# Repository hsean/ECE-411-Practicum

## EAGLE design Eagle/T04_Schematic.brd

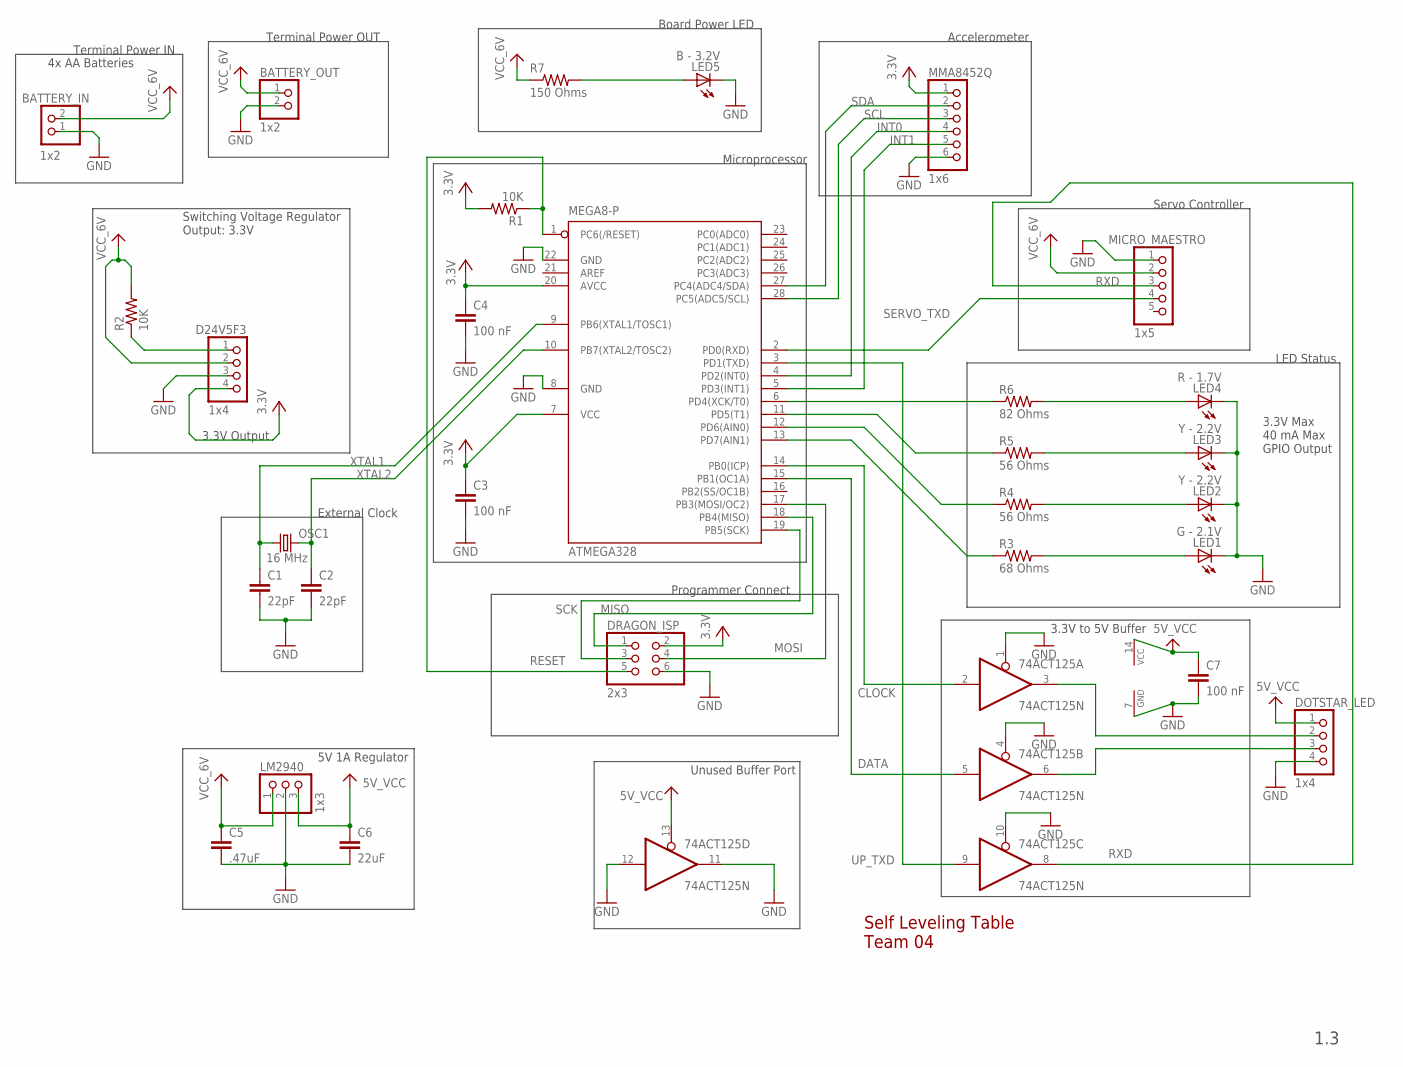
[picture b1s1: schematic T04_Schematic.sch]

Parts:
74ACT125: 74ACT125N; DIL14
ATMEGA328: MEGA8-P; DIL28-3
BATTERY_IN: 1x2; 1X02
BATTERY_OUT: 1x2; 1X02
C1, C2: 22pF; C1206
C3, C4, C7: 100 nF; C1206
C5: .47uF; C1206
C6: 22uF; C1206
D24V5F3: 1x4; 1X04
DOTSTAR_LED: 1x4; 1X04
DRAGON_ISP: 2x3; 2X03
LED1: G - 2.1V; 1206
LED2, LED3: Y - 2.2V; 1206
LED4: R - 1.7V; 1206
LED5: B - 3.2V; 1206
LM2940: 1x3; 1X03
MICRO_MAESTRO: 1x5; 1X05
MMA8452Q: 1x6; 1X06
OSC1: 16 MHz; HC49US
R1, R2: 10K; M1206
R3: 68 Ohms; R1206
R4, R5: 56 Ohms; R1206
R6: 82 Ohms; R1206
R7: 150 Ohms; R1206

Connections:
5V_VCC: 74ACT125.13 (OE), 74ACT125.14 (VCC), C6.1, C7.1, DOTSTAR_LED.1, LM2940.3
CLOCK: 74ACT125.2 (I), ATMEGA328.14 (PB0(ICP))
DATA: 74ACT125.5 (I), ATMEGA328.15 (PB1(OC1A))
GND: 74ACT125.1 (OE), 74ACT125.4 (OE), 74ACT125.7 (GND), 74ACT125.10 (OE), 74ACT125.11 (O), 74ACT125.12 (I), ATMEGA328.8 (GND), ATMEGA328.22 (GND), BATTERY_IN.1, BATTERY_OUT.2, C1.2, C2.2, C3.2, C4.2, C5.2, C6.2, C7.2, D24V5F3.3, DOTSTAR_LED.4, DRAGON_ISP.6, LED1.C, LED2.C, LED3.C, LED4.C, LED5.C, LM2940.2, MICRO_MAESTRO.1, MMA8452Q.6
INT0: ATMEGA328.4 (PD2(INT0)), MMA8452Q.4
INT1: ATMEGA328.5 (PD3(INT1)), MMA8452Q.5
MISO: ATMEGA328.18 (PB4(MISO)), DRAGON_ISP.1
MOSI: ATMEGA328.17 (PB3(MOSI/OC2)), DRAGON_ISP.4
unnamed: LED5.A, R7.2
unnamed: LED1.A, R3.2
unnamed: LED2.A, R4.2
unnamed: LED3.A, R5.2
unnamed: LED4.A, R6.2
unnamed: 74ACT125.3 (O), DOTSTAR_LED.2
unnamed: ATMEGA328.11 (PD5(T1)), R5.1
unnamed: ATMEGA328.12 (PD6(AIN0)), R4.1
unnamed: ATMEGA328.6 (PD4(XCK/T0)), R6.1
unnamed: ATMEGA328.13 (PD7(AIN1)), R3.1
unnamed: 74ACT125.6 (O), DOTSTAR_LED.3
RESET: ATMEGA328.1 (PC6(/RESET)), DRAGON_ISP.5, R1.1
RXD: 74ACT125.8 (O), MICRO_MAESTRO.3
SCK: ATMEGA328.19 (PB5(SCK)), DRAGON_ISP.3
SCL: ATMEGA328.28 (PC5(ADC5/SCL)), MMA8452Q.3
SDA: ATMEGA328.27 (PC4(ADC4/SDA)), MMA8452Q.2
SERVO_TXD: ATMEGA328.2 (PD0(RXD)), MICRO_MAESTRO.4
UP_TXD: 74ACT125.9 (I), ATMEGA328.3 (PD1(TXD))
VCC: ATMEGA328.7 (VCC), ATMEGA328.20 (AVCC), C3.1, C4.1, D24V5F3.4, DRAGON_ISP.2, MMA8452Q.1, R1.2
VCC_6V: BATTERY_IN.2, BATTERY_OUT.1, C5.1, D24V5F3.2, LM2940.1, MICRO_MAESTRO.2, R2.2, R7.1
V_REG_RESET: D24V5F3.1, R2.1
XTAL1: ATMEGA328.9 (PB6(XTAL1/TOSC1)), C1.1, OSC1.1
XTAL2: ATMEGA328.10 (PB7(XTAL2/TOSC2)), C2.1, OSC1.2

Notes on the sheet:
4x AA Batteries
1.3
3.3V Max 40 mA Max GPIO Output
3.3V Output
Terminal Power IN
Terminal Power OUT
Switching Voltage Regulator Output: 3.3V
Self Leveling Table Team 04
Accelerometer
Servo Controller
LED Status
Programmer Connect
Microprocessor
Board Power LED
External Clock
3.3V to 5V Buffer
5V 1A Regulator
Unused Buffer Port

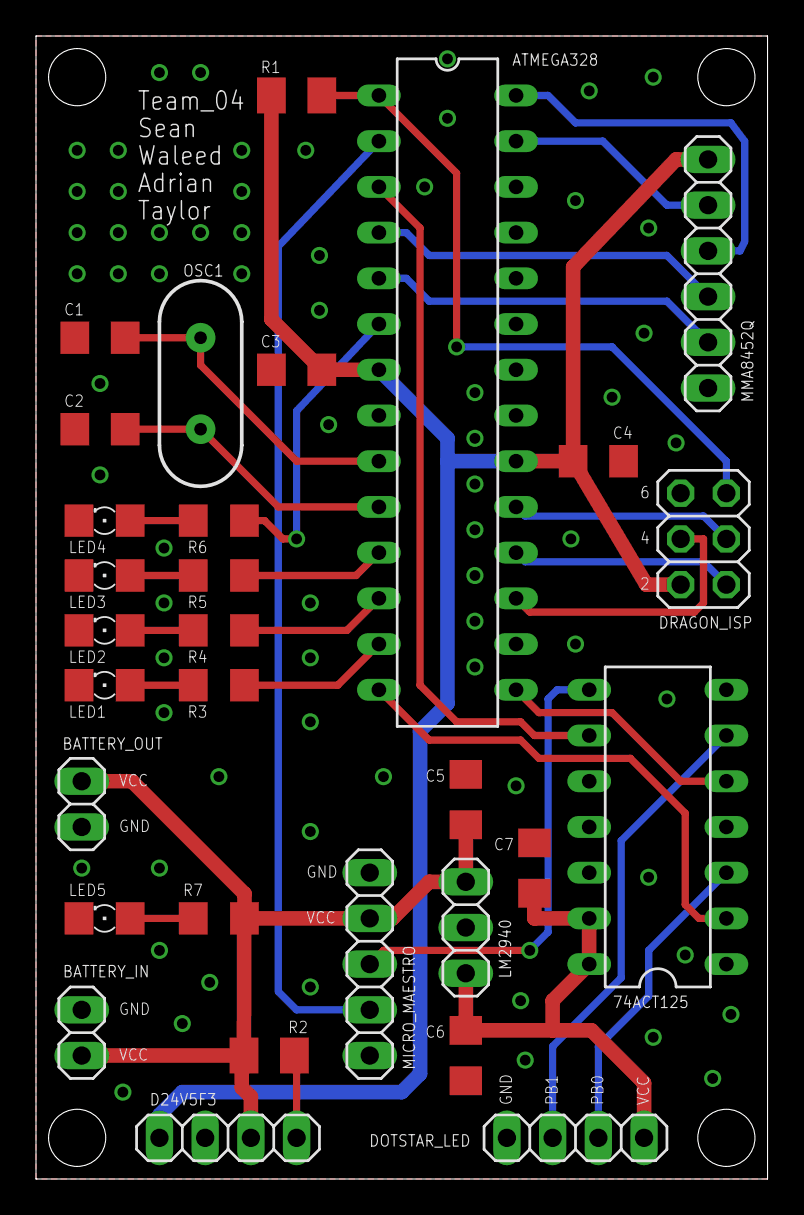
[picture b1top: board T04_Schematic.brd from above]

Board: 2 copper layers, 40.6 x 63.5 mm, 30 parts (0 on the bottom side), 31 nets.

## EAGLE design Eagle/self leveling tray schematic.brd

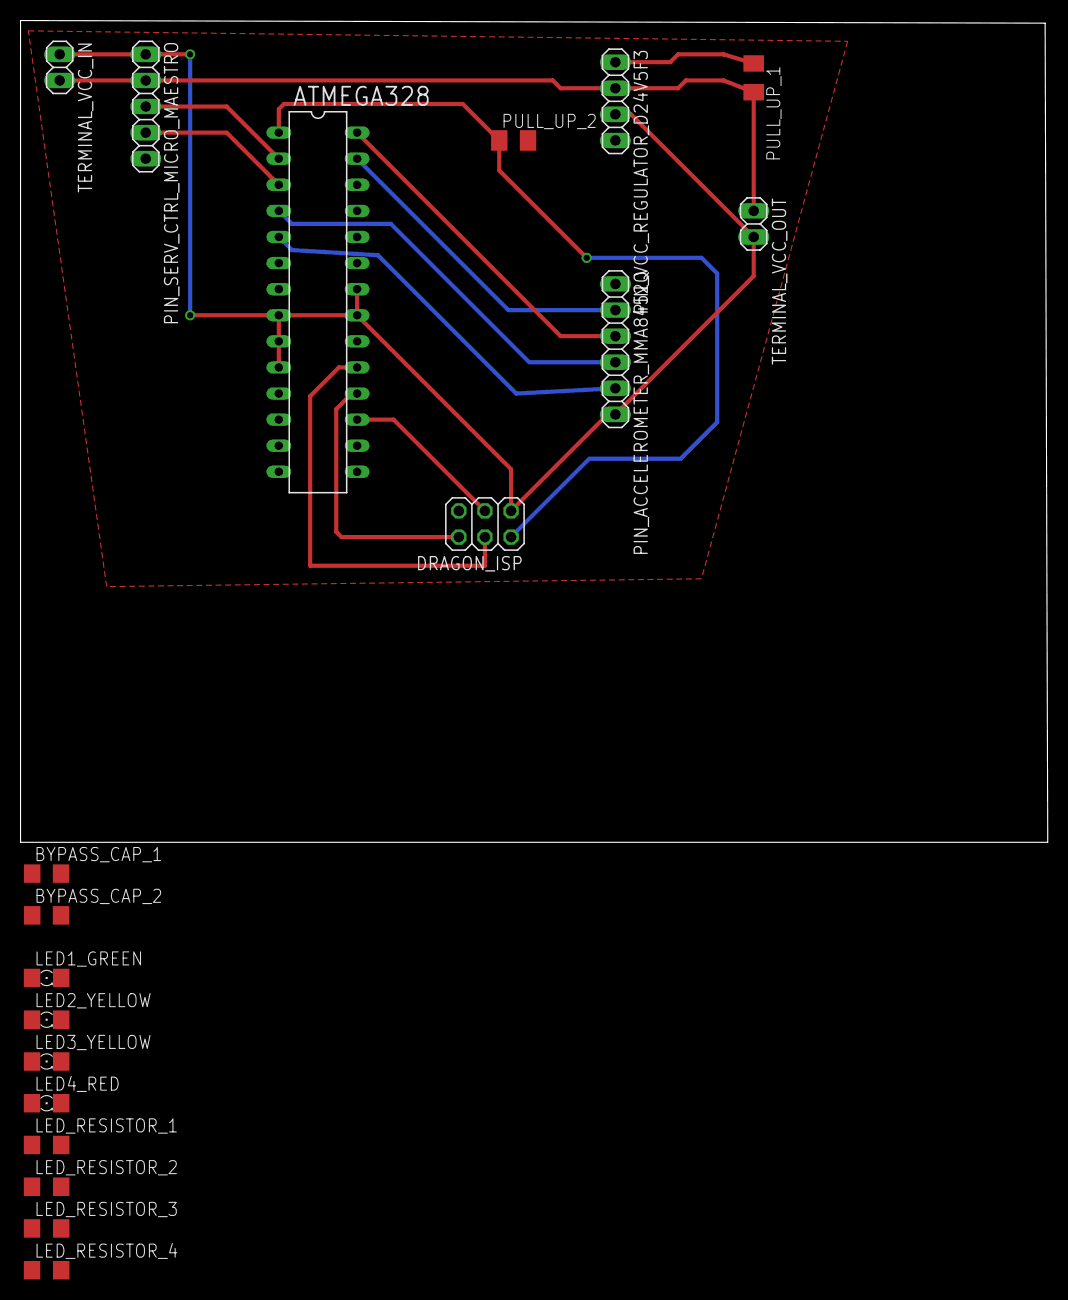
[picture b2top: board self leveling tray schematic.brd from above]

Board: 2 copper layers, 100.0 x 80.0 mm, 19 parts (0 on the bottom side), 22 nets.

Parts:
ATMEGA328: MEGA8-P; DIL28-3
BYPASS_CAP_1, BYPASS_CAP_2: 100 nF; C1206
DRAGON_ISP: 2x3; 2X03
LED1_GREEN, LED2_YELLOW, LED3_YELLOW, LED4_RED: TBD Voltage; 1206
LED_RESISTOR_1, LED_RESISTOR_2, LED_RESISTOR_3, LED_RESISTOR_4: TBD Resistance; R1206
PIN_ACCELEROMETER_MMA8452Q: 1x6; 1X06
PIN_SERV_CTRL_MICRO_MAESTRO: 1x5; 1X05
PIN_VCC_REGULATOR_D24V5F3: 1x4; 1X04
PULL_UP_1, PULL_UP_2: 10K; M1206
TERMINAL_VCC_IN: 1x2; 1X02
TERMINAL_VCC_OUT: 1x2; 1X02

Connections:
6V_BATTERY_VCC: PIN_SERV_CTRL_MICRO_MAESTRO.2, PIN_VCC_REGULATOR_D24V5F3.2, PULL_UP_1.2, TERMINAL_VCC_IN.2, TERMINAL_VCC_OUT.1
GND: ATMEGA328.8, ATMEGA328.9, ATMEGA328.10, ATMEGA328.14, ATMEGA328.15, ATMEGA328.16, ATMEGA328.21, ATMEGA328.22, ATMEGA328.23, ATMEGA328.24, ATMEGA328.25, ATMEGA328.26, BYPASS_CAP_1.2, BYPASS_CAP_2.2, DRAGON_ISP.1, LED1_GREEN.C, LED2_YELLOW.C, LED3_YELLOW.C, LED4_RED.C, PIN_ACCELEROMETER_MMA8452Q.6, PIN_SERV_CTRL_MICRO_MAESTRO.1, PIN_VCC_REGULATOR_D24V5F3.3, TERMINAL_VCC_IN.1, TERMINAL_VCC_OUT.2
INT0: ATMEGA328.4, PIN_ACCELEROMETER_MMA8452Q.4
INT1: ATMEGA328.5, PIN_ACCELEROMETER_MMA8452Q.5
LED_OUT_1: ATMEGA328.13, LED_RESISTOR_1.1
LED_OUT_2: ATMEGA328.12, LED_RESISTOR_2.1
LED_OUT_3: ATMEGA328.11, LED_RESISTOR_3.1
LED_OUT_4: ATMEGA328.6, LED_RESISTOR_4.1
MISO: ATMEGA328.18, DRAGON_ISP.6
MOSI: ATMEGA328.17, DRAGON_ISP.3
unnamed: LED1_GREEN.A, LED_RESISTOR_1.2
unnamed: LED2_YELLOW.A, LED_RESISTOR_2.2
unnamed: LED3_YELLOW.A, LED_RESISTOR_3.2
unnamed: LED4_RED.A, LED_RESISTOR_4.2
RESET: ATMEGA328.1, DRAGON_ISP.2, PULL_UP_2.1
RXD: ATMEGA328.2, PIN_SERV_CTRL_MICRO_MAESTRO.3
SCK: ATMEGA328.19, DRAGON_ISP.4
SCL: ATMEGA328.28, PIN_ACCELEROMETER_MMA8452Q.3
SDA: ATMEGA328.27, PIN_ACCELEROMETER_MMA8452Q.2
SHDN: PIN_VCC_REGULATOR_D24V5F3.1, PULL_UP_1.1
TXD: ATMEGA328.3, PIN_SERV_CTRL_MICRO_MAESTRO.4
VCC: ATMEGA328.7, ATMEGA328.20, BYPASS_CAP_1.1, BYPASS_CAP_2.1, DRAGON_ISP.5, PIN_ACCELEROMETER_MMA8452Q.1, PIN_VCC_REGULATOR_D24V5F3.4, PULL_UP_2.2

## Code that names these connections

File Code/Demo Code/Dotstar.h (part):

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	// set pin as output and Logic Level
	switch (pin)
	{
	case 9: // (PIN9 = PB6)
	{	DDRB |= (1 << PORTB6);  // set as output
	(level == eHIGH) ?      // if HIGH, set output HIGH, else set LOW
		(PORTB |= (1 << DDB6)) : (PORTB &= ~(1 << DDB6));
	break; }
	case 10: // (PIN10 = PB7)
	{	DDRB |= (1 << PORTB7);  // set as output
	(level == eHIGH) ?      // if HIGH, set output HIGH, else set LOW
		(PORTB |= (1 << DDB7)) : (PORTB &= ~(1 << DDB7));
	break; }
	case 14: // (PIN14 = PB0)
	{	DDRB |= (1 << PORTB0);  // set as output
	(level == eHIGH) ?      // if HIGH, set output HIGH, else set LOW
		(PORTB |= (1 << DDB0)) : (PORTB &= ~(1 << DDB0));
	break; }
	case 15: // (PIN15 = PB1)
	{	DDRB |= (1 << PORTB1);  // set as output
	(level == eHIGH) ?      // if HIGH, set output HIGH, else set LOW
		(PORTB |= (1 << DDB1)) : (PORTB &= ~(1 << DDB1));
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	(level == eHIGH) ?      // if HIGH, set output HIGH, else set LOW
		(PORTB |= (1 << DDB2)) : (PORTB &= ~(1 << DDB2));
	break; }
	case 17: // (PIN17 = PB3)
	{	DDRB |= (1 << PORTB3);  // set as output
	(level == eHIGH) ?      // if HIGH, set output HIGH, else set LOW
		(PORTB |= (1 << DDB3)) : (PORTB &= ~(1 << DDB3));
	break; }
	case 18: // (PIN18 = PB4)
	{	DDRB |= (1 << PORTB4);  // set as output
	(level == eHIGH) ?      // if HIGH, set output HIGH, else set LOW
		(PORTB |= (1 << DDB4)) : (PORTB &= ~(1 << DDB4));
	break; }
	case 19: // (PIN19 = PB5)
	{	DDRB |= (1 << PORTB5);  // set as output
	(level == eHIGH) ?      // if HIGH, set output HIGH, else set LOW
		(PORTB |= (1 << DDB5)) : (PORTB &= ~(1 << DDB5));
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	// set pin as output and Logic Level
	switch (pin)
	{
	case 1: // (PIN1 = PC6)
	{	DDRC |= (1 << PORTC6);  // set as output
	(level == eHIGH) ?      // if HIGH, set output HIGH, else set LOW
		(PORTC |= (1 << DDC6)) : (PORTB &= ~(1 << DDC6));
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	(level == eHIGH) ?      // if HIGH, set output HIGH, else set LOW
		(PORTC |= (1 << DDC3)) : (PORTB &= ~(1 << DDC3));
	break; }
	case 27: // (PIN27 = PC4)
	{	DDRC |= (1 << PORTC4);  // set as output
	(level == eHIGH) ?      // if HIGH, set output HIGH, else set LOW
		(PORTC |= (1 << DDC4)) : (PORTB &= ~(1 << DDC4));
	break; }
	case 28: // (PIN28 = PC5)
	{	DDRC |= (1 << PORTC5);  // set as output
	(level == eHIGH) ?      // if HIGH, set output HIGH, else set LOW
		(PORTC |= (1 << DDC5)) : (PORTB &= ~(1 << DDC5));
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	// set pin as output and Logic Level
	switch (pin)
	{
	case 2: // (PIN2 = PD0)
	{	DDRD |= (1 << PORTD0);  // set as output
	(level == eHIGH) ?      // if HIGH, set output HIGH, else set LOW
		(PORTD |= (1 << DDD0)) : (PORTB &= ~(1 << DDD0));
	break; }
	case 3: // (PIN3 = PD1)
	{	DDRD |= (1 << PORTD1);  // set as output
	(level == eHIGH) ?      // if HIGH, set output HIGH, else set LOW
		(PORTD |= (1 << DDD1)) : (PORTB &= ~(1 << DDD1));
	break; }
	case 4: // (PIN4 = PD2)
	{	DDRD |= (1 << PORTD2);  // set as output
	(level == eHIGH) ?      // if HIGH, set output HIGH, else set LOW
		(PORTD |= (1 << DDD2)) : (PORTB &= ~(1 << DDD2));
	break; }
	case 5: // (PIN5 = PD3)
	{	DDRD |= (1 << PORTD3);  // set as output
	(level == eHIGH) ?      // if HIGH, set output HIGH, else set LOW
		(PORTD |= (1 << DDD3)) : (PORTB &= ~(1 << DDD3));
	break; }
	case 6: // (PIN6 = PD4)
	{	DDRD |= (1 << PORTD4);  // set as output
	(level == eHIGH) ?      // if HIGH, set output HIGH, else set LOW
		(PORTD |= (1 << DDD4)) : (PORTB &= ~(1 << DDD4));
	break; }
	case 11: // (PIN11 = PD5)
	{	DDRD |= (1 << PORTD5);  // set as output
	(level == eHIGH) ?      // if HIGH, set output HIGH, else set LOW
		(PORTD |= (1 << DDD5)) : (PORTB &= ~(1 << DDD5));
	break; }
	case 12: // (PIN12 = PD6)
	{	DDRD |= (1 << PORTD6);  // set as output
	(level == eHIGH) ?      // if HIGH, set output HIGH, else set LOW
		(PORTD |= (1 << DDD6)) : (PORTB &= ~(1 << DDD6));
	break; }
	case 13: // (PIN13 = PD7)
	{	DDRD |= (1 << PORTD7);  // set as output
	(level == eHIGH) ?      // if HIGH, set output HIGH, else set LOW
		(PORTD |= (1 << DDD7)) : (PORTB &= ~(1 << DDD7));
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	// set pin as input
	switch (pin)
	{
	case 9: // (PIN9 = PB6)
	{	DDRB &= ~(1 << PORTB6); break; } // set as input
	case 10: // (PIN10 = PB7)
	{	DDRB &= ~(1 << PORTB7); break; }// set as input
	case 14: // (PIN14 = PB0)
	{	DDRB &= ~(1 << PORTB0); break; } // set as input
	case 15: // (PIN15 = PB1)
	{	DDRB &= ~(1 << PORTB1); break; } // set as input
	case 16: // (PIN16 = PB2)
	{	DDRB &= ~(1 << PORTB2); break; } // set as input
	case 17: // (PIN17 = PB3)
	{	DDRB &= ~(1 << PORTB3); break; } // set as input
	case 18: // (PIN18 = PB4)
	{	DDRB &= ~(1 << PORTB4); break; } // set as input
	case 19: // (PIN19 = PB5)
	{	DDRB &= ~(1 << PORTB5); break; } // set as input
	}
}
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	// set pin as input
	switch (pin)
	{
	case 1: // (PIN1 = PC6)
	{	DDRC &= ~(1 << PORTC6); break; } // set as input
	case 23: // (PIN23 = PC0)
	{	DDRC &= ~(1 << PORTC0); break; } // set as input
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	{	DDRC &= ~(1 << PORTC2); break; } // set as input
	case 26: // (PIN26 = PC3)
	{	DDRC &= ~(1 << PORTC3); break; } // set as input
	case 27: // (PIN27 = PC4)
	{	DDRC &= ~(1 << PORTC4); break; } // set as input
	case 28: // (PIN28 = PC5)
	{	DDRC &= ~(1 << PORTC5); break; } // set as input
	}
}
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	// set pin as input
	switch (pin)
	{
	case 2: // (PIN2 = PD0)
	{	DDRD &= ~(1 << PORTD0); break; } // set as input
	case 3: // (PIN3 = PD1)
	{	DDRD &= ~(1 << PORTD1); break; } // set as input
	case 4: // (PIN4 = PD2)
	{	DDRD &= ~(1 << PORTD2); break; } // set as input
	case 5: // (PIN5 = PD3)
	{	DDRD &= ~(1 << PORTD3); break; } // set as input
	case 6: // (PIN6 = PD4)
	{	DDRD &= ~(1 << PORTD4); break; }  // set as input
	case 11: // (PIN11 = PD5)
	{	DDRD &= ~(1 << PORTD5); break; } // set as input
	case 12: // (PIN12 = PD6)
	{	DDRD &= ~(1 << PORTD6); break; } // set as input
	case 13: // (PIN13 = PD7)
	{	DDRD &= ~(1 << PORTD7); break; } // set as input
	}
}
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
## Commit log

2015-10-13 Adding Homework 2. includes 4 ideas and project proposal
2015-10-19 adding some files
    Adding microcontroller datasheet and hw3 rough draft
2015-10-19 Added Datasheets
    Added documentation for the parts I purchased.
2015-10-20 Adding Datasheet for processor we may use
2015-10-20 Concept 1
    Added some pictures for a concept I put together in solidworks just so
    everyone has a similar image in their minds. Of course this concept
    does not include everything we discussed.
2015-10-21 Eagle files
    Just adding some documentation for Eagle CAD
2015-10-21 Revert "Adding Datasheet for processor we may use"
    This reverts commit 9a58cd5520d000a9ef4d838af932a524d4ed95d9.
2015-10-21 Spacing concept picture
    Just adding a picture that helps narrow the spacing on top of the base.
    An 8 inch base seems to work.
2015-10-25 Design Specification
    Updating the design specification document
2015-10-25 Final Version 1
    Adding version from weekend meeting
2015-10-25 Taylor Test Commit
    It's blank!
2015-10-25 Done Testing
    Still blank.
2015-10-25 testing
    testing thingy
2015-10-25 finished test
2015-10-25 Solidworks Models
    Adding models I have been working with. I need help with the final ball
    joint.
2015-10-27 Weekly Progress Report
    Added all weeks to a single, viewable, text file
2015-10-27 voltage regulator info
    added datasheet and schematic for Pololu Voltage Regulator
2015-10-28 Eagle Schematic 1.0
    First draft schematic.
    Taylor Griffin
2015-10-28 Added Screw equation
    Just a simple equation to figure out the diameter of threaded bar
2015-10-28 Schematic & Layout
    Fixed ERC errors in schematic.
    Created (practice?) layout.
    Taylor Griffin
2015-10-31 Schematic Version 1.2
    Added changes suggested by Andrew.
    Added LEDs and grounded unused GPIO.
    Email from Andrew:
    Hi Taylor!
    > Could you take a look at our current schematic? It passes ERC right
    now,
2015-10-31 Schematic Update
    Minor changes to Text formatting for names/values etc.
2015-10-31 Revert "delete"
    This reverts commit d87595251c5fcdd05d3273c181309bee60e2e347.
2015-10-31 adding gant chart
    just adding this for HW4
2015-10-31 Moving Gant
    Just moving the gant chart into a folder for clarity
2015-10-31 Gant chart
    updated roles
2015-11-02 Create External Clock
    The first option is the most recommended one
2015-11-02 Update External Clock
2015-11-02 Schematic Updates
    Updated with better supply layout and more organization.
    Also changed filename to have team name.
    Still Need: Oscillator, LEDs, UART review
2015-11-03 Potential crystal oscillator to use with atmega328
2015-11-03 Updating gant chart and adding crystal wire guide
    just updating this documentation
2015-11-04 Adding Schedule
    This is a blank microsoft project file
2015-11-04 Repository Management
    Re-organizing the folders and names of some of the files.
2015-11-04 Added Project Schedule
    Lots of tasks.
2015-11-04 Added PDF schedule and fixed folder name.
2015-11-06 Added images of us testing components
2015-11-08 Small Schematic Update
    Minor tweaks, notes
2015-11-08 Example code for programming the ATmega328 for blinking an LED
2015-11-08 Edited the code folder structuer, added first version of USART interface
2015-11-09 Schematic and Layout
    Added DRC passing PCB layout.
    Updated Schematic, added buffer for 5V LED control.
2015-11-09 Remove Old Files
2015-11-09 Solidworks Parts
    Adding all the parts needed for concept 5 and the rendered images of
    concept 5
2015-11-09 DRC Error Free Layout + Schematic Update
    Made changes to layout based on feedback from class.
    Added linear regulator to schematic for 5V supply.
    Will need group review.
2015-11-10 current code for testing uart
2015-11-10 edited test uart code initialization to be more detailed.
2015-11-10 Added Feedback Changes to Layout
2015-11-10 Model and WPR Update
    Compiled all of are weekly progress reports into a single text file and
    added some new concept pictures for a redesign of the model.
2015-11-10 Got UART Code Working
    Adrian's Working Code
2015-11-11 Added batch servo control function
2015-11-11 renamed working_usart_test_code.c to test_communications.c and added steps for communicating with accelerometer using waleed's i2c functions
2015-11-12 New Concept Pictures
    Moved the LEDs. Changed acrylic to 1/8 inch. Added different colored
    trays.
2015-11-13 TWI DONE
    Step 1: Turn it on.
    Step 2: ???
    Step 3: PROFIT.
2015-11-14 Final(?) Layout
    Increase board size for more room to solder.
    Improved power signal layout.
    Added missing GND and VCC to Dotstar LEDs.
2015-11-14 Fixed Typo in Component Name
2015-11-15 Block Diagram Draft
    Just a powerpoint file
2015-11-15 Concept Images
    Now with screws!
2015-11-15 Minor Tweaks and Fixes
2015-11-15 edited the level 1 block diagram for overal system
2015-11-15 Added Andrew's Changes and Some more Silk Screen ID
    Hi Taylor,
    > We've been getting great feedback from you on our schematic/layout and
    I
    > was wondering if you could take one last look at our layout to see if
    we
    > missed anything major before we submit it.
2015-11-15 Fixed Typo
2015-11-15 Fixed Silkscreen Position as Rendered by OSHPark
2015-11-15 Minor Changes for OSHPark -- PRINTED
    Moved vias and text to make it pretty.
    -- This File Uploaded to Print!!!
2015-11-18 completed homework 5
2015-11-18 saved as hw pdf
2015-11-19 v0.1 of the bill of materials
    Fill this out more as we purchase parts. The spreadsheet can be found
    in google sheets.
2015-11-20 Number Mapping Code
    Added some example code for mapping one range of integers to another.
    This example uses angles and PWM values.
2015-11-20 Improved number mapping function
    changed the number mapping function to be more general and better
    documented. The original function is still in the .cpp file as well as
    the commented out test code.
2015-11-20 Added class UML diagram
    just a basic diagram to get the overall structure of the program
    started. I don't know much about UML so the symbols and associations
    may be incorrect. The editor is violet UML from sourceforge.
2015-11-21 Initial commit of main program. Stuff to add: LED strip code, error checking for status LEDs, calculation of servo positions, possibly change to fast read mode.
2015-11-23 Added example code we used to test the accelerometer in arduino
2015-11-24 Code and diagram update
    Added some untested code of the class implementation and updated the UML
    Class Diagram.
2015-11-25 Added Homework 6 test plan
2015-11-25 test code to control 3 servos with accelerometer x y z measurements
2015-11-25 edited twi communication code to hopefully work with fast read mode (ignore lsb registers)
2015-11-25 accl_controlled_servos_test.c: edited outdated function comment mainProgram.c: updated setMultipleTargets() function to work with an array of entries rather than fixed number
2015-11-26 Acrylic after laser cut
    Adding the pictures of the acrylic I took on my phone on Wednesday.
2015-11-30 just an ignore
2015-11-30 Re-adding deleted file
    accidentally removed powerpoint file while merging. Adding the file
    back.
2015-12-01 updating and testing class code
    I made some updates where needed to test the class code. I added a main
    file and tested each class by altering the classes and then checking the
    data. Just run main to test.
2015-12-02 Example LED Strip Code
    Added code for arduino and raspberry pi from adafruit.com
2015-12-02 Some Servo Notes
2015-12-02 edited code for accelerometer fast mode
2015-12-05 Dotstar Code Partially Finished
    So, I worked on the dotstar code and some new code for configuring pins.
    will need to test pin configuration code in Atmel studio since all of
    the register names really confuse Visual Studio.
2015-12-05 Current test code for putty: allows you to print the expected servo angle movements to screen. Other test code also in this file but commented out.
2015-12-06 continuing to work on dotstar
    some more progress
2015-12-06 Adrian's newest code
    Some math errors were fixed
2015-12-07 A couple changes to class implementation
2015-12-07 Dotstar C
2015-12-07 Working Dotstar code
    This includes the working C file along with the are test from Monday.
2015-12-09 Reorganizing
    Getting rid of old solidworks files and organizing pictures a little
    better.
2015-12-09 Updating Bill of Materials
    Just adding more parts from the parts spreadsheet.
2015-12-09 Added new renderings
    I thought these renderings will already in the git Repo but they were
    not.
2015-12-10 updating model
2015-12-10 Added Resistor and LED Voltages
2015-12-10 reformatted, finished main program
2015-12-10 Updated Schedule
2015-12-10 cleaned up code
    I got rid of a commented out function and got rid of pointless comments
    in main. I also added some comments for Dotstar but the LED code and
    servo calculations could use some more documentation.
2015-12-10 Updated specifications for current project
2015-12-10 Added Example code references, and made edits to mainprogram (added some \#defines, fixed some commends
2015-12-10 Final List of Components
    This is a complete Bill of Materials.
2015-12-10 Uploaded PPT
2015-12-11 updated block diagrams
2016-07-11 power point to PDF
    Added a PDF version of the power point presentation for easy reading on
    github

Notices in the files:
parts and their libraries:
SparkFun-FreqCtrl: Licensing: Creative Commons ShareAlike 4.0 International - https://creativecommons.org/licenses/by-sa/4.0
